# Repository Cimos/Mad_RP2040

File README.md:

# Mad_RP2040

A small RP2040-based keypad PCB. Originally a minimal 2-key board to build confidence with the RP2040 ahead of a full-size keyboard, it has since grown into a 4x4 "anything" keypad with a rotary encoder and per-key RGB.

**Status:** Rev B (4x4) — fabricated November 2025; controller, USB and SK6812MINI-E chain verified, but a matrix wiring error past row 1 / col 1 needs cut-and-bodge to fix on existing units. The fix is not yet in `main`, so fabbing from `main` today reproduces the same bodge. Rev A (2-key) was fabricated and tested; archived under [`resources/rev_a/`](resources/rev_a/).

The encoder footprint is on the board but has not yet been populated/tested.

## Hardware

- **MCU:** Raspberry Pi RP2040 (QFN-56)
- **Flash:** W25Q128JV (16 MB QSPI)
- **Clock:** 12 MHz ECS-2520MV SMD oscillator
- **Power:** USB-C input, NCP1117-3.3 LDO, ECMF02-2 common-mode filter / ESD protection
- **Switches:** 16x Kailh Choc v2 hotswap (12 mm) in a 4x4 matrix with 1N4148W diodes
- **Encoder:** 1x EC12 rotary encoder with switch
- **Lighting:** Per-key SK6812MINI / SK6812MINI-E RGB LEDs
- **Split support:** TRS interlink (JST-SHL/GH connectors) plus a solder-jumper hand-detect selector
- **Programming:** ARM SWD via Tag-Connect TC2030-NL footprint

Datasheets for the major parts live in [`resources/datasheets/`](resources/datasheets/).

## Repository layout

```
Mad_RP2040.kicad_pro     # KiCad project
Mad_RP2040.kicad_sch     # Top-level schematic
Mad_RP2040.kicad_pcb     # Board layout
Mad_RP2040.kicad_dru     # Design rules
Controller_RP2040.kicad_sch
MCU_RP2040.kicad_sch
Switches.kicad_sch       # Hierarchical sheets
localLib.pretty/         # Project-local footprints
mad_lib/                 # Submodule with shared symbols/footprints
resources/               # Datasheets, enclosure STEP, fabrication outputs
build-panel.yaml         # KiBot panel config (1x2)
options.yaml             # KiBot global options
```

The repo uses a git submodule for `mad_lib`; clone with:

```sh
git clone --recurse-submodules https://github.com/Cimos/Mad_RP2040.git
```

## Build & CI

GitHub Actions in [`.github/workflows/`](.github/workflows/) drive the build via [Cimos/kibot-config](https://github.com/Cimos/kibot-config):

- `build-pcb-action.yaml` — fabrication outputs (gerbers, drills, BOM, position files)
- `build-images-action.yaml` — 2D top/bottom renders
- `build-cad-action.yaml` — STEP / 3D CAD export
- `build-panel-action.yaml` — KiKit panelization (2 cols x 1 row, see `build-panel.yaml`)
- `build-diff-action.yaml` — visual diff against the base branch
- `build-video-action.yaml` — turntable / fly-through video

Each workflow uploads its results as a GitHub Actions artifact on every push.

## Firmware

Keymap and configuration are kept in separate repos:

- [`Cimos/qmk_config`](https://github.com/Cimos/qmk_config) — [QMK](https://qmk.fm/) keymap
- [`Cimos/zmk-config`](https://github.com/Cimos/zmk-config) — [ZMK](https://zmk.dev/) keymap

## Enclosure

FreeCAD-exported cases live in [`resources/enclosures/`](resources/enclosures/):

- `MadRP2040 2-Key Case.step` — Rev A test board
- `MadRP2040 Anything Case.stl` — Rev B 4x4 anything keypad

Released board CAD (STEP) snapshots live under [`resources/rev_a/`](resources/rev_a/).

## Renders

Generated by the `build-images`, `build-cad` and `build-panel` workflows from the latest `main`.

| | |
|---|---|
|  |  |
|  |  |

## License

Released under the [MIT License](LICENSE). Copyright (c) 2023 Simon Maddison.

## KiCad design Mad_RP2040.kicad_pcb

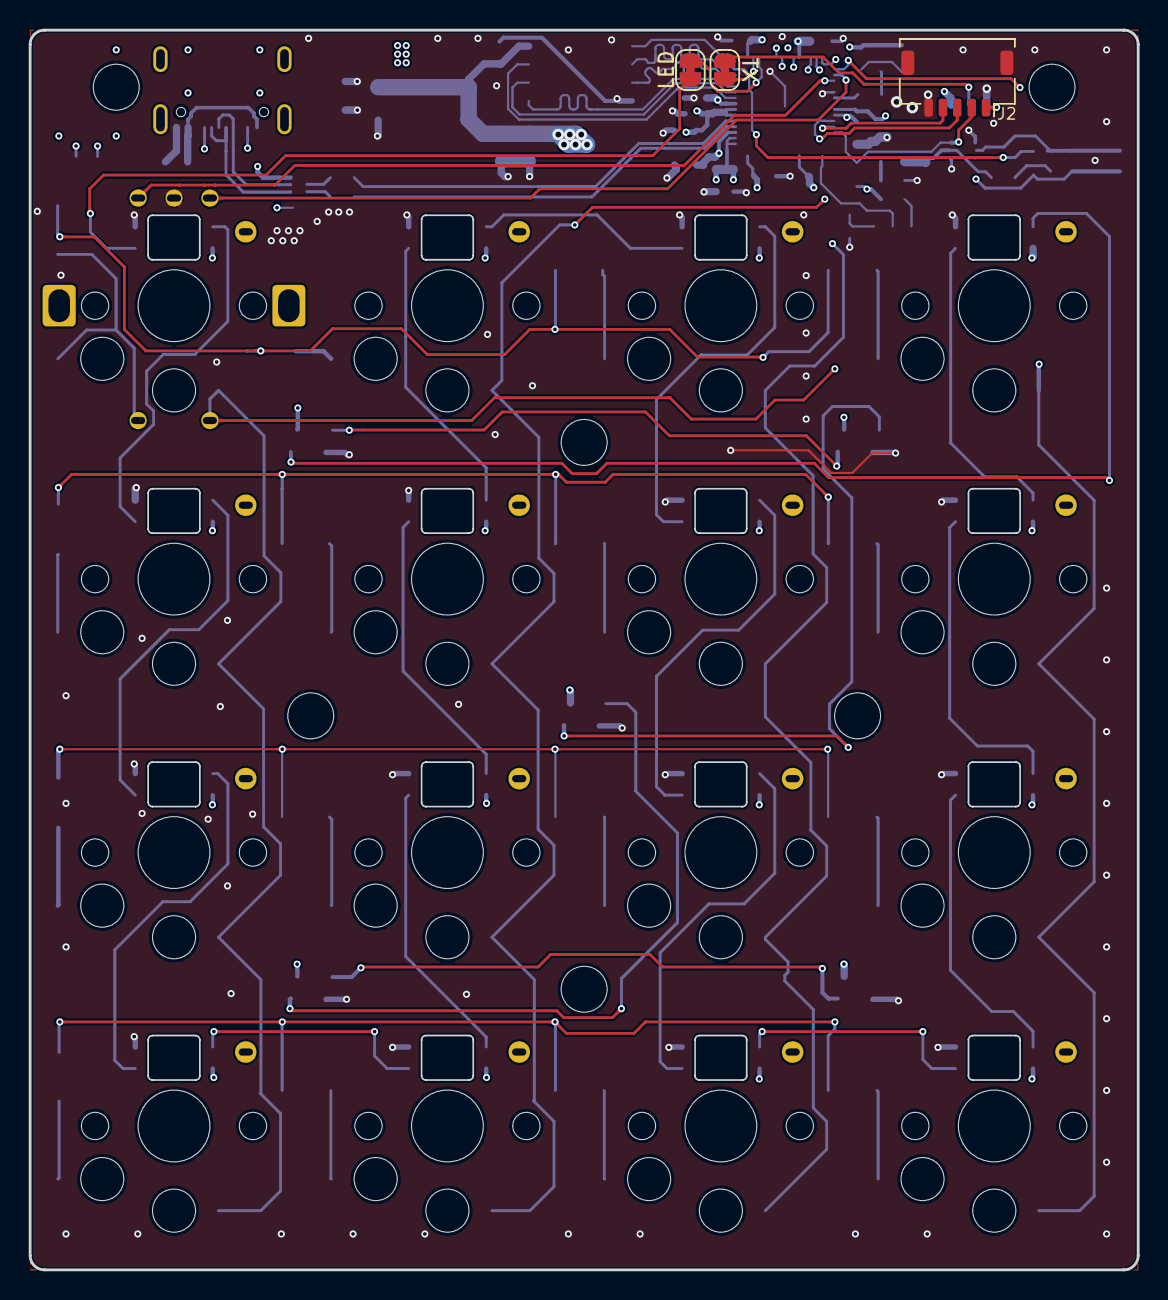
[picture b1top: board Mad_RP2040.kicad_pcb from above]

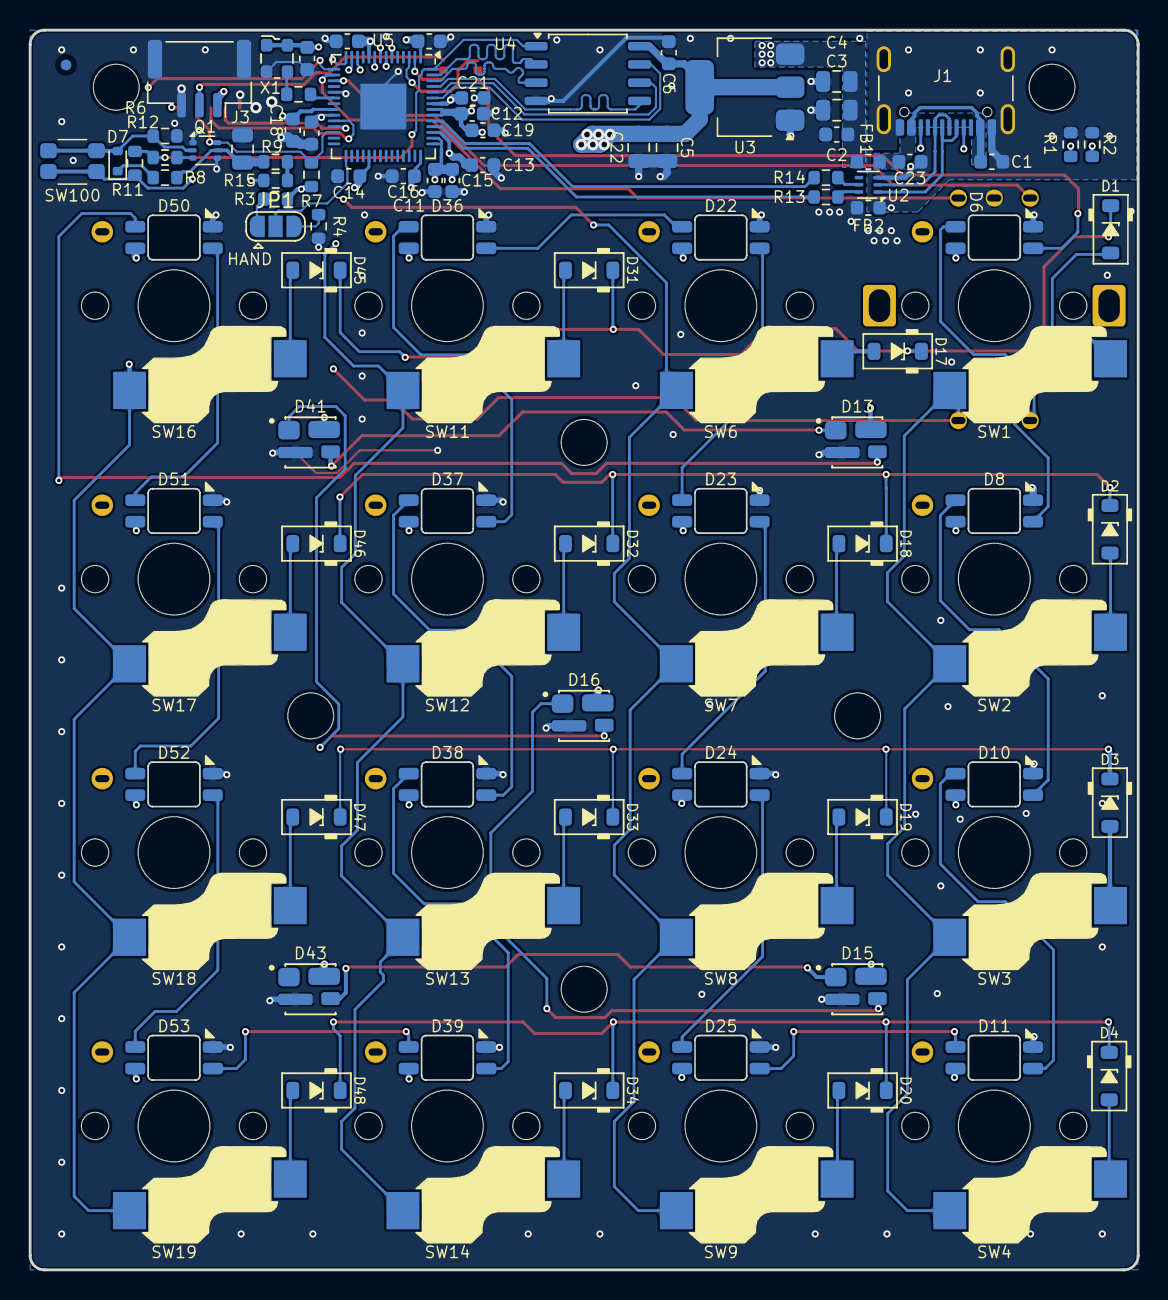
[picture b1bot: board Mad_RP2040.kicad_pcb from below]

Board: 4 copper layers, 77.2 x 86.4 mm, 117 parts (107 on the bottom side), 83 nets.

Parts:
C1, C2, C6, C7, C10, C11, C12, C14, C16, C17, C18, C19, C20, C21, C23: 100nF; C_0603_1608Metric
C3, C4, C5, C9, C22: 10uF; C_0805_2012Metric
C13, C15: 1uF; C_0603_1608Metric
D1, D2, D3, D4, D17, D18, D19, D20, D31, D32, D33, D34, D45, D46, D47, D48: 1N4148W; D_SOD-123
D6, D8, D10, D11, D22, D23, D24, D25, D36, D37, D38, D39, D50, D51, D52, D53: SK6812_MINI_E; SK6812MINI-E
D7: RB520S30; D_SOD-523
D13, D15, D16, D41, D43: SK6812MINI; SK6812MINI-012
FB1, FB2: BLM18PG330SN1D; L_0603_1608Metric
FID1: Fiducial; Fiducial_0.75mm_Mask1.5mm
H2, H4, H6, H8, H10, H11: MountingHole_Pad; MountingHole_3.2mm_M3
J1: USB_C_Receptacle; USB_C_Receptacle_GCT_USB4105-xx-A_16P_TopMnt_Horizontal
J2: Conn_ARM_SWD_TagConnect_TC2030-NL; JST_SHL_SM05B-SHLS-TF_1x05-1MP_P1.00mm_Horizontal
J3: TRS; JST_GH_SM03B-GHS-TB_1x03-1MP_P1.25mm_Horizontal
JP1: Split Hand Detect Selector; SolderJumper-3_P1.3mm_Open_RoundedPad1.0x1.5mm
JP2, JP3: SolderJumper_2_Bridged; SolderJumper-2_P1.3mm_Bridged_RoundedPad1.0x1.5mm
Q1: 2N7002PV,115; SOT-666
R1, R2, R3, R4: 5K1; R_0603_1608Metric
R6, R7, R11: 10K; R_0603_1608Metric
R8, R9, R15: 51K; R_0603_1608Metric
R10, R12: 1K; R_0603_1608Metric
R13, R14: 27R; R_0603_1608Metric
SW1: RotaryEncoder_Switch; keyswitch_choc12_hotswap_1u_rotary_encoder_ec12
SW2, SW3, SW4, SW6, SW7, SW8, SW9, SW11, SW12, SW13, SW14, SW16, SW17, SW18, SW19: SW_SPST; keyswitch_choc12_hotswap_1u
SW100: EVPAA202K; EVP-AA202K
T1, T2, T3, T4: Tab
U0: PCB; BOM
U2: ECMF02-2AMX6; ST_UQFN-6L_1.5x1.7mm_P0.5mm
U3: NCP1117-3.3; SOT-223-3_TabPin2
U4: W25Q128JVSIQ; SOIC-8_5.23x5.23mm_P1.27mm
U5: RP2040; QFN-56-1EP_7x7mm_P0.4mm_EP3.2x3.2mm
X1: ECS-2520MVLC-120-CN; Oscillator_SMD_ECS_2520MV-xxx-xx-4Pin_2.5x2.0mm

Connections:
+5V: C2.1, C3.1, C4.1, D6.1 (VDD), D8.1 (VDD), D10.1 (VDD), D11.1 (VDD), D13.2 (VDD), D15.2 (VDD), D16.2 (VDD), D22.1 (VDD), D23.1 (VDD), D24.1 (VDD), D25.1 (VDD), D36.1 (VDD), D37.1 (VDD), D38.1 (VDD), D39.1 (VDD), D41.2 (VDD), D43.2 (VDD), D50.1 (VDD), D51.1 (VDD), D52.1 (VDD), D53.1 (VDD), FB1.2, J3.1, U3.3 (VI)
/Col0: SW1.S2, SW2.2 (B), SW3.2 (B), SW4.2 (B), U5.12 (GPIO9)
/Col1: SW6.2 (B), SW7.2 (B), SW8.2 (B), SW9.2 (B), U5.13 (GPIO10)
/Col2: SW11.2 (B), SW12.2 (B), SW13.2 (B), SW14.2 (B), U5.14 (GPIO11)
/Col3: SW16.2 (B), SW17.2 (B), SW18.2 (B), SW19.2 (B), U5.15 (GPIO12)
/LED: D6.4 (DIN), JP3.2 (B)
/PreFIlterGND: C1.2, C23.2, FB2.1, J1.A1 (GND), J1.A12 (GND), J1.B1 (GND), J1.B12 (GND), J1.S1 (SHIELD), R1.2, R2.2, U2.3 (GND)
/PreFilter_USB_D+: J1.A6 (D+), J1.B6 (D+), U2.2 (D-_in)
/PreFilter_USB_D-: J1.A7 (D-), J1.B7 (D-), U2.1 (D+_in)
/REA: SW1.A, U5.16 (GPIO13)
/REB: SW1.B, U5.17 (GPIO14)
/RP2040/3V3: C5.1, C6.1, C7.1, C10.1, C11.1, C12.1, C14.1, C15.2, C16.1, C17.1, C18.1, C19.1, C22.1, J2.1, R3.1, R7.2, R11.2, SW100.1, U3.2 (VO), U4.8 (VCC), U5.1 (IOVDD), U5.10 (IOVDD), U5.22 (IOVDD), U5.33 (IOVDD), U5.42 (IOVDD), U5.43 (ADC_AVDD), U5.44 (VREG_VIN), U5.48 (USB_VDD), U5.49 (IOVDD), X1.1 (Tri-State), X1.4 (VDD)
/RP2040/LED: JP3.1 (A), U5.3 (GPIO1)
/RP2040/RP2040/1V1: C13.2, C20.1, C21.1, U5.23 (DVDD), U5.45 (VREG_VOUT), U5.50 (DVDD)
/RP2040/RP2040/GPIO18: JP1.2 (C), U5.29 (GPIO18)
/RP2040/RP2040/QSPI_SCLK: U4.6 (CLK), U5.52 (QSPI_SCLK)
/RP2040/RP2040/QSPI_SD0: U4.5 (DI(IO0)), U5.53 (QSPI_SD0)
/RP2040/RP2040/QSPI_SD1: U4.2 (DO(IO1)), U5.55 (QSPI_SD1)
/RP2040/RP2040/QSPI_SD2: U4.3 (IO2), U5.54 (QSPI_SD2)
/RP2040/RP2040/QSPI_SD3: U4.7 (IO3), U5.51 (QSPI_SD3)
/RP2040/RP2040/QSPI_~CS: R11.1, R12.2, U4.1 (~CS), U5.56 (QSPI_SS_N)
/RP2040/RP2040/USB_D+: R14.2, U5.47 (D+)
/RP2040/RP2040/USB_D-: R13.2, U5.46 (D-)
/RP2040/RP2040/XTAL_IN: R10.1, U5.20 (XTAL_IN)
/RP2040/SWCLK: J2.3, U5.24 (SWCLK)
/RP2040/SWDIO: J2.4, U5.25 (SWDIO)
/RP2040/TX: JP2.1 (A), U5.2 (GPIO0)
/RP2040/USB_D+: R14.1, U2.5 (D-_out)
/RP2040/USB_D-: R13.1, U2.6 (D+_out)
/RP2040/~RST: J2.2, Q1.6 (D), R7.1, U5.26 (~RUN)
/Row0: D1.1 (K), D17.1 (K), D31.1 (K), D45.1 (K), U5.6 (GPIO4)
/Row1: D2.1 (K), D18.1 (K), D32.1 (K), D46.1 (K), U5.7 (GPIO5)
/Row2: D3.1 (K), D19.1 (K), D33.1 (K), D47.1 (K), U5.8 (GPIO6)
/Row3: D4.1 (K), D20.1 (K), D34.1 (K), D48.1 (K), U5.9 (GPIO7)
/TX: J3.2, JP2.2 (B)
GND: C2.2, C3.2, C4.2, C5.2, C6.2, C7.2, C9.2, C10.2, C11.2, C12.2, C13.1, C14.2, C15.1, C16.2, C17.2, C18.2, C19.2, C20.2, C21.2, C22.2, D6.3 (GND), D8.3 (GND), D10.3 (GND), D11.3 (GND), D13.4 (GND), D15.4 (GND), D16.4 (GND), D22.3 (GND), D23.3 (GND), D24.3 (GND), D25.3 (GND), D36.3 (GND), D37.3 (GND), D38.3 (GND), D39.3 (GND), D41.4 (GND), D43.4 (GND), D50.3 (GND), D51.3 (GND), D52.3 (GND), D53.3 (GND), FB2.2, J2.5, J2.MP (MountPin), J3.3, J3.MP (MountPin), Q1.1 (S), Q1.4 (S), R4.2, R6.1, R15.2, SW1.C, U3.1 (GND), U4.4 (GND), U5.19 (TESTEN), U5.57 (GND), X1.2 (GND)
unnamed: D1.2 (A), SW1.S1
unnamed: D2.2 (A), SW2.1 (A)
unnamed: D3.2 (A), SW3.1 (A)
unnamed: D4.2 (A), SW4.1 (A)
unnamed: D6.2 (DOUT), D8.4 (DIN)
unnamed: D7.2 (A), Q1.2 (G), R6.2, SW100.2
unnamed: D7.1 (K), R8.2
unnamed: D8.2 (DOUT), D10.4 (DIN)
unnamed: D10.2 (DOUT), D11.4 (DIN)
unnamed: D11.2 (DOUT), D25.4 (DIN)
unnamed: D13.1 (DIN), D50.2 (DOUT)
unnamed: D13.3 (DOUT), D41.1 (DIN)
unnamed: D15.1 (DIN), D16.3 (DOUT)
unnamed: D15.3 (DOUT), D43.1 (DIN)
unnamed: D16.1 (DIN), D41.3 (DOUT)
unnamed: D17.2 (A), SW6.1 (A)
unnamed: D18.2 (A), SW7.1 (A)
unnamed: D19.2 (A), SW8.1 (A)
unnamed: D20.2 (A), SW9.1 (A)
unnamed: D22.4 (DIN), D23.2 (DOUT)
unnamed: D22.2 (DOUT), D36.4 (DIN)
unnamed: D23.4 (DIN), D24.2 (DOUT)
unnamed: D24.4 (DIN), D25.2 (DOUT)
unnamed: D31.2 (A), SW11.1 (A)
unnamed: D32.2 (A), SW12.1 (A)
unnamed: D33.2 (A), SW13.1 (A)
unnamed: D34.2 (A), SW14.1 (A)
unnamed: D36.2 (DOUT), D37.4 (DIN)
unnamed: D37.2 (DOUT), D38.4 (DIN)
unnamed: D38.2 (DOUT), D39.4 (DIN)
unnamed: D39.2 (DOUT), D53.4 (DIN)
unnamed: D45.2 (A), SW16.1 (A)
unnamed: D46.2 (A), SW17.1 (A)
unnamed: D47.2 (A), SW18.1 (A)
unnamed: D48.2 (A), SW19.1 (A)
unnamed: D50.4 (DIN), D51.2 (DOUT)
unnamed: D51.4 (DIN), D52.2 (DOUT)
unnamed: D52.4 (DIN), D53.2 (DOUT)
unnamed: J1.A5 (CC1), R1.1
unnamed: J1.B5 (CC2), R2.1
unnamed: JP1.1 (A), R3.2
unnamed: JP1.3 (B), R4.1
unnamed: Q1.3 (D), R12.1
unnamed: C9.1, Q1.5 (G), R8.1, R9.1
unnamed: R9.2, R15.1
unnamed: R10.2, X1.3 (OUT)
VBUS: C1.1, C23.1, FB1.1, J1.A4 (VBUS), J1.A9 (VBUS), J1.B4 (VBUS), J1.B9 (VBUS)

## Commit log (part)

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2024-08-06 Move RP2040 controller into local
2024-08-06 Annotation update
2024-08-06 Board update
2024-08-06 Add github action
2024-08-06 remove crumbcatcher name from files
2024-08-07 Update github actions
    Remove double up on actions
    Remove kibot config file to what the action is looking for
    Update date on title block
    Update github actions
    update github action
    update schematic
2024-08-07 Finish off part placement
2024-08-07 Add todo
2024-08-08 Update github action
2024-08-08 Cleanup bom, remove spaces and lcsc fields
2024-08-08 update workflow to v4
2024-08-08 Update Models, Finalize LED selections, add backlight, ...
    add mounting holes, add fids, cleanup
2024-08-09 BOM update, add lcsc pn to componenets.
2024-08-10 BOM update
2024-08-10 BOM consolidation
2024-08-11 Update design rules
2024-08-11 Add dru, start routing
2024-08-11 Fix some errors, more routing
2024-08-11 Update todo's
2024-08-13 Finish off routing
2024-08-15 Minor silk update
2024-08-17 #1 Add panel file and updated github action
2024-08-17 #1 Rejig github actions
2024-08-17 #1 Test for if panel file exhists
2024-08-18 Update job descriptions
2024-08-18 Add board tabs
2024-08-18 adjust panel array
2024-08-18 Add verbose
2024-08-18 Try using container method for building datapack
2024-08-18 Test custom action
2024-08-18 Update workflow
2024-08-19 Minor track work update and
2024-08-22 Add USB diff trace calcs and reroute usb traces
2024-08-22 Enable verbose
2024-08-22 Comment out second build
2024-08-23 Update value to mpn
2024-10-10 #2 Update panel tabs
2025-04-05 1 Add Panel (#2)
    * #1 Add panel file and updated github action
    * #1 Test for if panel file exhists
    * #1 Rejig github actions
    * Update job descriptions
    * Add board tabs
    * adjust panel array
2025-04-05 Update usb data pins, update to fix 3v3 reg not adj
2025-04-05 Remove Xtal test pad, update PCB
2025-04-05 Update footprint on back light SK6812MINI LED, add more back lights.
2025-04-05 Update PCB back light
2025-04-12 Expand board to 4x5, update rev to b
2025-04-14 Update github workflow
2025-04-29 Rough placement of components. Remove one layer of keys (4x4 -> 4x3)
2025-04-30 More placement, start routing, fix up some schematic connections
2025-04-30 Update tabs
2025-04-30 Update github actions to use main not master for kibot-config checkout
2025-05-01 Review Schematic, Add TRS connector. Continue routing
2025-05-03 Continue routing.
2025-07-28 Finish off routing, clear DRC/ERC's, add missing datasheets
2025-07-28 Update panel size, fix kikit tab link, adjust tab placement and size
2025-07-28 Fix PCB edge
2025-07-28 Update workflow builds
2025-07-28 Rename workflow jobs, use new refactored panelization
2025-07-28 Uses panel file when generating panel datapack
2025-07-31 Update tabs and panel
2025-08-02 Update to 0603 components
    Update part of PCB
    Finish re-routing 0603
    adjust workflow for refactored kibot-config
    fill zones to fix FIDs
2025-08-02 Always try to upload artifacts
2025-08-03 refactor documents folder
2025-08-04 add rev_a step models for future reference
    Add github actions for images, cad, diff. Rename pcb action
2025-08-04 fetch whole repo for diff
2025-08-04 Remove BOM consolidation comment
2025-08-04 Update github actions
2025-08-04 Add Video action
2025-08-04 test out new action
    Update actions
2025-08-04 Update actions
2025-08-05 Update schematic date
2025-08-06 Updates component supplier information
    Replaces supplier part numbers with LCSC, Digikey and Mouser numbers
    for better component sourcing and availability tracking.
    Removes redundant "Supplier PN", "Substitute", and "LCSC PN" properties.
    Hides some BOM columns in the project settings.
    Also fixes a couple of pin UUIDs and config flags.
2025-08-06 Adds digikey and mouser part numbers to components
    Adds digikey and mouser properties to components in the .kicad_pcb file.
    Renames "LCSC PN" property to "LCSC" and "Config" property to be more descriptive in certain cases, such as "-LCSC_BOM" or "Interface".
    This allows for easier sourcing and BOM management.
2025-08-06 pcb: Hide non-essential text on fabrication layers
2025-08-06 pcb: Standardize footprint text styling and refine placement
2025-08-06 KiCad: Remove redundant BOM properties from PCB file
2025-08-06 feat(kicad): Clear datasheet and description for oscillator footprint
2025-08-06 chore(kicad): Update UUIDs for footprint graphical elements
2025-08-06 Updates BOM sort order
    Changes the BOM sort order to be sorted by reference designator in descending order.
    This makes the BOM easier to read and follow.
    Increase build images action verbosity
2025-08-06 sch: Update schematic creation/modification date
2025-08-28 [PCB] Minor track work update
2025-09-01 [PCB] Change switch diodes to 1N4148W and update PCB
2025-09-02 [PCB] Update Diode footprint to have silk diode.
2025-09-02 [PCB] Fix min track spacing
2025-09-16 Add Rev A enclosure
2025-09-16 Larger 4x4 Anything Keypad (#3)
    * Update usb data pins, update to fix 3v3 reg not adj
    * Remove Xtal test pad, update PCB
    * Update footprint on back light SK6812MINI LED, add more back lights.
    * Update PCB back light
    * Expand board to 4x5, update rev to b
    * Update github workflow
2025-11-15 Minor updates after building and testing boards. Added key caps to model
2026-04-21 Update date
2026-05-10 Expand README with hardware, build, and enclosure details
    Replaces the one-line description with a standard project README:
    overview, hardware summary, repo layout, CI workflow rundown,
    enclosure pointer, and license. Includes a TODO placeholder for a
    PCB render URL once the build-images artifact is published.
    https://claude.ai/code/session_011Mt2xiQHKvSeekri8G1S4w
2026-05-10 Workflow PRs target main not master
2026-05-10 Move keycap STEP out of footprint lib
2026-05-10 Add firmware section to README
2026-05-10 Note rev A status in README
2026-05-10 Add Rev B render gallery, encoder note, ZMK config link, anything case
    - Replace TODO PCB-render placeholder with top 3/4 hero
    - Add Renders section: top/bottom 3/4 + straight, 1x2 panel
    - Update Status to Rev B with matrix-bug caveat
    - Note encoder footprint not yet populated/tested
    - Link both Cimos/qmk_config and Cimos/zmk-config in Firmware
    - Swap enclosure: v44 case -> 2-Key Case + Anything Case
2026-05-10 Expand README (#4)
    * Expand README with hardware, build, and enclosure details
    Replaces the one-line description with a standard project README:
    overview, hardware summary, repo layout, CI workflow rundown,
    enclosure pointer, and license. Includes a TODO placeholder for a
    PCB render URL once the build-images artifact is published.
    https://claude.ai/code/session_011Mt2xiQHKvSeekri8G1S4w
2026-05-10 Workflow PRs target main not master (#5)
2026-05-10 Move keycap STEP out of footprint lib (#6)
2026-05-16 Add DRC rule for minimum plated slot width
    Enforces JLCPCB's 0.5mm minimum plated slot width. The condition
    matches plated through-hole pads whose X and Y hole dimensions
    differ (i.e. slots), and constrains the smaller dimension via the
    hole_size minimum.
2026-05-17 Add DRC rule for minimum non-plated slot width
    Enforces JLCPCB's 1.0mm minimum non-plated slot width. Matches NPTH
    mechanical pads whose X and Y hole dimensions differ (i.e. slots),
    and constrains the smaller dimension via the hole_size minimum.
2026-05-17 Add DRC rule for hole-to-board-edge clearance
    Enforces JLCPCB's 1mm minimum distance between drilled holes (PTH,
    NPTH, vias) and the board edge. Castellated pads are excluded
    since they intentionally sit on the edge. The minimum board size
    note (10x10mm) is left as documentation since it cannot be
    expressed as a DRC constraint.
2026-05-17 Document that NPTH pad inner-diameter rule is already enforced
    The TODO at the top of the file asked for a rule ensuring NPTH pad
    inner diameter is 0.4-0.5mm larger than the drill. The existing
    NPTH Annular Ring rule already enforces this (annular_width min
    0.25mm => pad diameter at least 0.5mm larger than the hole).
    Removes the dangling TODO and moves the JLCPCB context as a
    comment above the rule that enforces it.
2026-06-16 ci: publish build artifacts to GitHub Release on version tags (#11)
    Add release.yaml workflow triggered on `v*` tags. Rebuilds the PCB
    datapack, 3D model, 2D images, and panel datapack (when build-panel.yaml
    is present) from the tagged commit via the Cimos/kibot-config action,
    zips each into a versioned archive, and publishes a GitHub Release with
    auto-generated notes and the archives attached.
2026-06-16 ci: bump actions/checkout v4 -> v5 across all workflows (#12)
    Resolves the Node.js 20 deprecation annotation. checkout@v5 is a drop-in
    for v4 here (only the default Node runtime changed; all inputs used are
    unchanged). upload-artifact stays at v4 (no v5 exists yet).
2026-06-16 ci: consolidate build workflows + hygiene (concurrency, paths, perms, pinning) (#13)
    * ci: consolidate build workflows + hygiene (concurrency, paths, perms, pin)
    - Consolidate build-pcb/cad/images into one matrix workflow (build-datapacks.yaml)
    with panel as a second job; delete the 4 superseded files.
    - Add concurrency cancel-in-progress to CI workflows (serialize, no waste).
    - Add path filters so doc/CI-only commits don't trigger board builds.
    - Trim triggers: build on PRs + main (was every branch push); diff is PR-only.
2026-06-16 ci: warn-only ERC/DRC design-review gate with PR comment (#14)
    * ci: add warn-only ERC/DRC design-review gate with PR comment
    New design-review.yaml runs KiCad ERC + DRC on PRs (re-enabling the checks
    that the shared kibot-config options.yaml disables, via a project-local
    design-review.kibot.yaml). DRC uses the custom Mad_RP2040.kicad_dru. The
    gate is warn-only (continue-on-error) and posts/updates a single summary
    comment on the PR via the gh CLI (no third-party actions). Reports are
2026-06-16 ci: kicad-happy AI design review (fork-safe, SHA-pinned, no AI/egress) (#15)
    * ci: add kicad-happy AI design-review (fork-safe, SHA-pinned, no AI/egress)
    Adds the deterministic tier of aklofas/kicad-happy as a PR design review,
    following the security audit's required mitigations:
    - Fork-safe two-workflow pattern: analysis runs on pull_request with a
    read-only token; comment posts via workflow_run with pull-requests:write
    and runs no third-party analysis code.
2026-06-16 ci: stitch video frames into MP4; add CLAUDE.md project/CI guide (#17)
    - build-video-action.yaml: add a non-fatal ffmpeg step that renumbers the
    rendered PNG frames and assembles output_video/<project>-3d.mp4 (padded to
    even dims, yuv420p). Resolves the long-standing TODO. First real run is on
    the next push to main (push-only trigger; couldn't be CI-tested on a PR).
    - CLAUDE.md: document the CI/CD architecture, release process, action-pinning
    policy, the two design-review gates, kicad-happy security invariants, and
2026-06-22 ci: make release workflow idempotent and dispatchable for any tag
    The publish step used 'gh release create', which fails if the release already
    exists — that's what errored the first v0.0.1 run after the build succeeded.
    Make it create-or-update: upload assets with --clobber when the release exists,
    create it otherwise.
    Add workflow_dispatch with a 'tag' input so a release can be built for any
    existing tag, including older tags whose commit predates this workflow (the
